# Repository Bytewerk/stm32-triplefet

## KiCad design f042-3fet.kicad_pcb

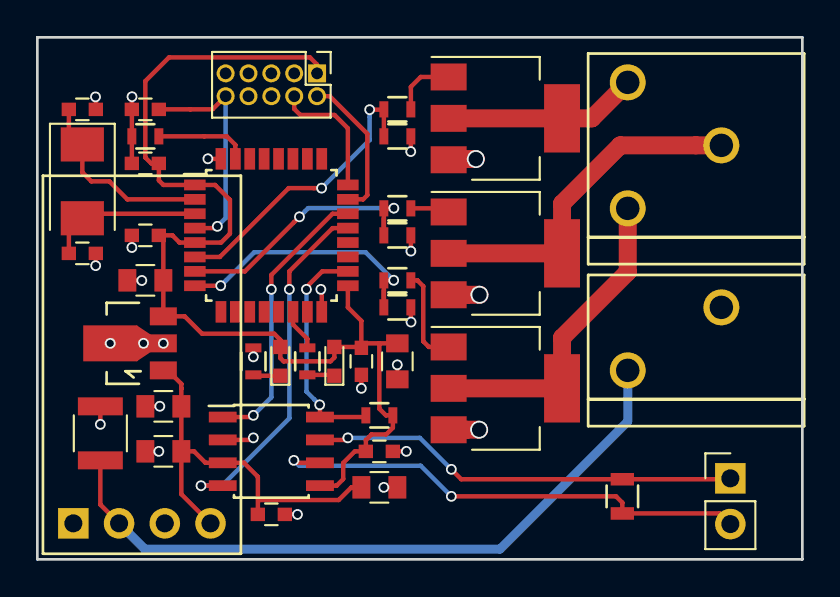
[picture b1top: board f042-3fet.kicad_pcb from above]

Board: 2 copper layers, 42.5 x 29.0 mm, 39 parts (0 on the bottom side), 27 nets.

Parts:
C1: 10uF/25V; C_1210
C2, C3, C4, C11: 10uF; C_0805
C5, C7: 18pF; C_0603
C6, C8, C9, C10, C12, C13: 100nF; C_0603
C14: 1uF; C_0805
D1: green; LED_0603
D2: red; LED_0603
P1: CONN_01X02; Pin_Header_Straight_1x02_Pitch2.54mm
P2: CONN_01X02; TE-1-2834011-2
P3: CONN_01X03; TE-1-2834011-3
Q1, Q2, Q3: Q_NMOS_GDSD; SOT-223
R1, R2, R6, R7, R8: 1K; R_0603
R3, R4, R5, R9, R10: 10K; R_0603
R11: 120R; R_0805
U1: china-switcher
U2: MCP1754ST-3302E/MB; SOT89-3_Housing
U3: STM32F042K6Tx; LQFP-32_7x7mm_Pitch0.8mm
U4: TJA1051T/3; SOIC-8_3.9x4.9mm_Pitch1.27mm
X1: CONN_CORTEX_SWD; Pin_Header_Straight_2x05_Pitch1.27mm
Y1: 8Mhz; Crystal_SMD_Abracon_ABM3-2pin_5.0x3.2mm

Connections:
+3V3: C4.1, C8.1, C9.1, C10.1, C11.1, C12.1, D1.2, D2.2, R10.2, U2.3, U3.1, U3.5, U3.17, U4.5, X1.1
+5V: C2.1, C3.1, C13.1, C14.1, U1.4, U2.1, U4.3
+12V: C1.1, P2.1, U1.2
/CAN_TRX/CAN_H: P1.1, R11.1, U4.7
/CAN_TRX/CAN_L: P1.2, R11.2, U4.6
/STM32F0x2-LQFP32/BOOT0: R9.2, U3.31
/STM32F0x2-LQFP32/NRST: C6.1, U3.4, X1.10
/STM32F0x2-LQFP32/SWCLK: U3.24, X1.4
/STM32F0x2-LQFP32/SWDIO: U3.23, X1.2
CAN_RXD: U3.21, U4.4
CAN_S: R10.1, U3.18, U4.8
CAN_TXD: U3.22, U4.1
GND: C1.2, C2.2, C3.2, C4.2, C5.2, C6.2, C7.2, C8.2, C9.2, C10.2, C11.2, C12.2, C13.2, C14.2, P2.2, Q1.3, Q2.3, Q3.3, R1.2, R3.1, R4.1, R5.1, R9.1, U1.3, U2.2, U3.16, U3.32, U4.2, X1.3, X1.5, X1.9
unnamed: C5.1, U3.2, Y1.1
unnamed: C7.1, U3.3, Y1.2
unnamed: D1.1, R1.1
unnamed: D2.1, R2.1
unnamed: Q1.1, R6.1
unnamed: Q2.1, R7.1
unnamed: Q3.1, R8.1
OUT0: P3.3, Q1.2, Q1.4
OUT0_UC: R3.2, R6.2, U3.6
OUT1: P3.2, Q2.2, Q2.4
OUT1_UC: R4.2, R7.2, U3.7
OUT2: P3.1, Q3.2, Q3.4
OUT2_UC: R5.2, R8.2, U3.8
USRLED: R2.2, U3.14

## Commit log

2017-02-24 first production
